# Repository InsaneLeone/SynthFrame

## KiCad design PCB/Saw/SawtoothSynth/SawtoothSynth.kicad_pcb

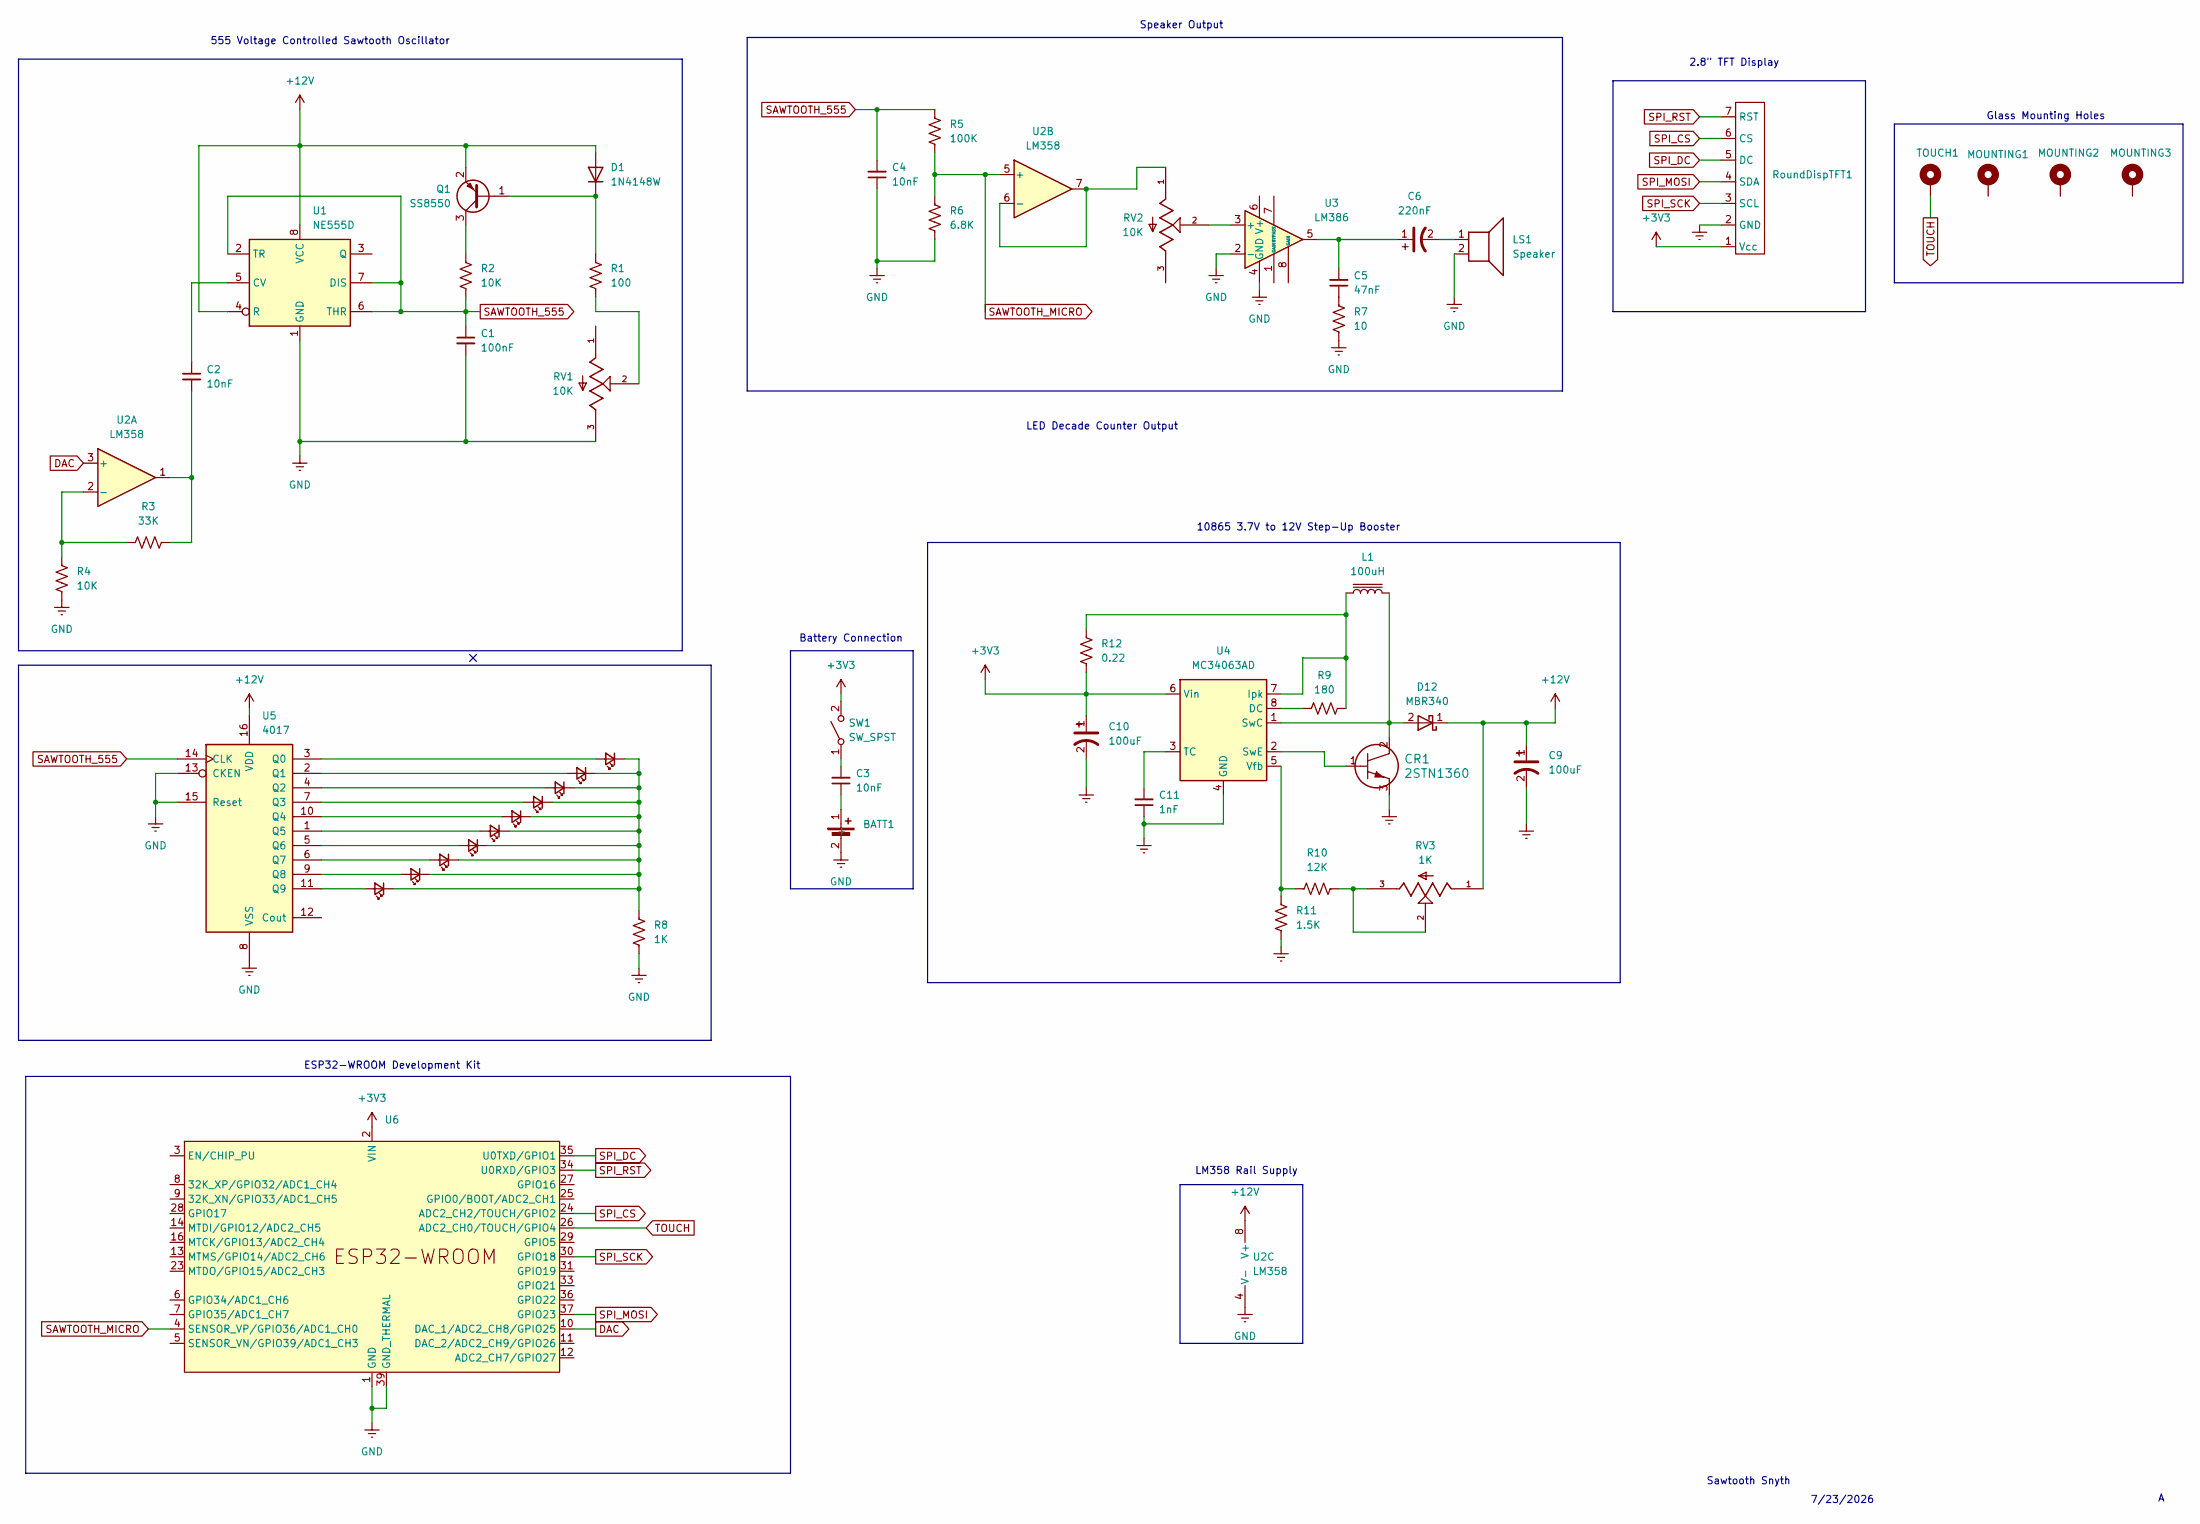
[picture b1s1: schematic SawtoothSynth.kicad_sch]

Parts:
BATT1: 18650PC Battery Holder 1043P
C1: 100nF; C_0805_2012Metric
C2, C3, C4: 10nF; C_0805_2012Metric
C5: 47nF; C_0805_2012Metric
C6: 220nF; 25THV220M8X10.5
C8: 25THV220M8X10.5; CAP_J-V_8X10P5_RUB
C9, C10: 100uF; 865060445005
C11: 1nF; C_0805_2012Metric
CR1: 2STN1360; SOT-223-3_TabPin2
D1: 1N4148W; D_SOD-123
D2, D3, D4, D5, D6, D7, D8, D9, D10, D11: LED_Small; LED_0805_2012Metric_Pad1.15x1.40mm_HandSolder
D12: MBR340; D_SMA
L1: 100uH; IND_BOURNS_SRN8040
LS1: Speaker; PinHeader_1x02_P2.54mm_Vertical
MOUNTING1, MOUNTING2, MOUNTING3: MountingHole_Pad; MountingHole_4.3mm_M4_Pad_TopBottom
Q1: SS8550; SOT-23
R1: 100; R_0805_2012Metric
R2, R4: 10K; R_0805_2012Metric
R3: 33K; R_0805_2012Metric
R5: 100K; R_0805_2012Metric
R6: 6.8K; R_0805_2012Metric
R7: 10; R_0805_2012Metric
R8: 1K; R_0805_2012Metric
R9: 180; R_0805_2012Metric
R10: 12K; R_0805_2012Metric
R11: 1.5K; R_0805_2012Metric
R12: 0.22; R_0805_2012Metric
RV1, RV2: 10K; TRIM_TC33X-2-103E
RV3: 1K; TRIM_TC33X-2-103E
RoundDispTFT1: 1.28___Round_TFT
SW1: SW_SPST; SW_SPST_Toggle
TOUCH1: MountingHole_Pad; MountingHole_4.3mm_M4_Pad_TopBottom
U1: NE555D; SOIC-8_3.9x4.9mm_P1.27mm
U2: LM358; LM358DR2G
U3: LM386; LM386MX-1NOPB
U4: MC34063AD; SOIC-8_3.9x4.9mm_P1.27mm
U5: 4017; CD4017BM96
U6: ESP32-WROOM_Devkit

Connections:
+3V3: C10.1, R12.1, RoundDispTFT1.1 (Vcc), SW1.2 (B), U4.6 (Vin), U6.2 (VIN)
+12V: C9.1, D1.2 (A), D12.1 (K), Q1.2 (E), RV3.1, U1.4 (R), U1.8 (VCC), U2.8 (V+), U5.16 (VDD)
DAC: U2.3 (+), U6.10 (DAC_1/ADC2_CH8/GPIO25)
GND: BATT1.2 (-), C1.2, C4.1, C9.2, C10.2, C11.1, CR1.3, LS1.2, R4.2, R6.2, R7.2, R8.2, R11.1, RV1.3, RoundDispTFT1.2 (GND), U1.1 (GND), U2.4 (V-), U3.2 (-), U3.4 (GND), U4.4 (GND), U5.8 (VSS), U5.13 (CKEN), U5.15 (Reset), U6.1 (GND), U6.15 (GND), U6.38 (GND), U6.39 (GND_THERMAL)
unnamed: BATT1.1 (+), C3.1
unnamed: C2.2, R3.2, U2.1
unnamed: C5.1, R7.1
unnamed: C5.2, C6.1, U3.5
unnamed: C6.2, LS1.1
unnamed: D1.1 (K), Q1.1 (B), R1.1
unnamed: D2.2 (A), U5.2 (Q1)
unnamed: D3.2 (A), U5.3 (Q0)
unnamed: D4.2 (A), U5.4 (Q2)
unnamed: D5.2 (A), U5.7 (Q3)
unnamed: D6.2 (A), U5.10 (Q4)
unnamed: D7.2 (A), U5.1 (Q5)
unnamed: D8.2 (A), U5.5 (Q6)
unnamed: D9.2 (A), U5.6 (Q7)
unnamed: D10.2 (A), U5.9 (Q8)
unnamed: D2.1 (K), D3.1 (K), D4.1 (K), D5.1 (K), D6.1 (K), D7.1 (K), D8.1 (K), D9.1 (K), D10.1 (K), D11.1 (K), R8.1
unnamed: D11.2 (A), U5.11 (Q9)
unnamed: CR1.2, D12.2 (A), L1.2, U4.1 (SwC)
unnamed: Q1.3 (C), R2.1
unnamed: R1.2, RV1.2
unnamed: R10.2, RV3.2, RV3.3
unnamed: C3.2, SW1.1 (A)
unnamed: C2.1, U1.5 (CV)
unnamed: R3.1, R4.1, U2.2 (-)
unnamed: RV2.1, U2.6 (-), U2.7
unnamed: RV2.2, U3.3 (+)
unnamed: R9.1, U4.8 (DC)
unnamed: L1.1, R9.2, R12.2, U4.7 (Ipk)
unnamed: CR1.1, U4.2 (SwE)
unnamed: C11.2, U4.3 (TC)
unnamed: R10.1, R11.2, U4.5 (Vfb)
SAWTOOTH_555: C1.1, C4.2, R2.2, R5.1, U1.2 (TR), U1.6 (THR), U1.7 (DIS), U5.14 (CLK)
SAWTOOTH_MICRO: R5.2, R6.1, U2.5 (+), U6.4 (SENSOR_VP/GPIO36/ADC1_CH0)
SPI_CS: RoundDispTFT1.6 (CS), U6.24 (ADC2_CH2/TOUCH/GPIO2)
SPI_DC: RoundDispTFT1.5 (DC), U6.35 (U0TXD/GPIO1)
SPI_MOSI: RoundDispTFT1.4 (SDA), U6.37 (GPIO23)
SPI_RST: RoundDispTFT1.7 (RST), U6.34 (U0RXD/GPIO3)
SPI_SCK: RoundDispTFT1.3 (SCL), U6.30 (GPIO18)
TOUCH: TOUCH1.1, U6.26 (ADC2_CH0/TOUCH/GPIO4)

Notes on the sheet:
LM358 Rail Supply
10865 3.7V to 12V Step-Up Booster
ESP32-WROOM Development Kit
Glass Mounting Holes
2.8" TFT Display
Speaker Output
555 Voltage Controlled Sawtooth Oscillator
7/23/2026
Battery Connection
LED Decade Counter Output
Sawtooth Snyth

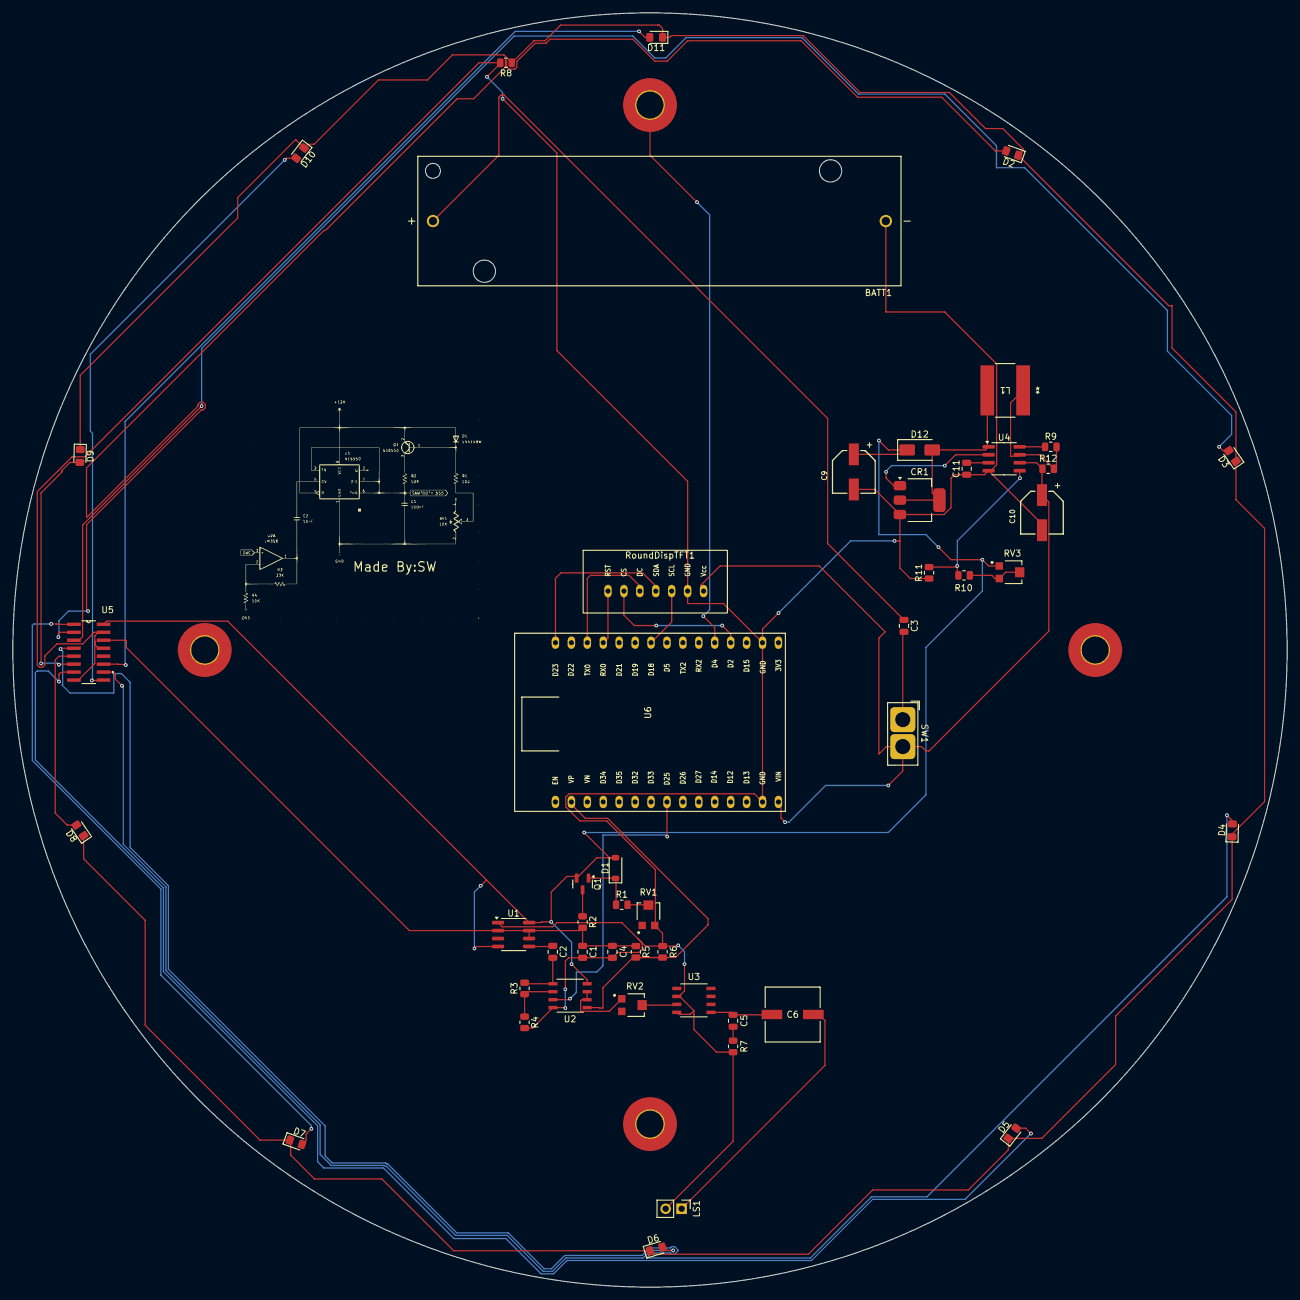
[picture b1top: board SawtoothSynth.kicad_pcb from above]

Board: 2 copper layers, 203.2 x 203.2 mm, 53 parts (0 on the bottom side), 43 nets.
